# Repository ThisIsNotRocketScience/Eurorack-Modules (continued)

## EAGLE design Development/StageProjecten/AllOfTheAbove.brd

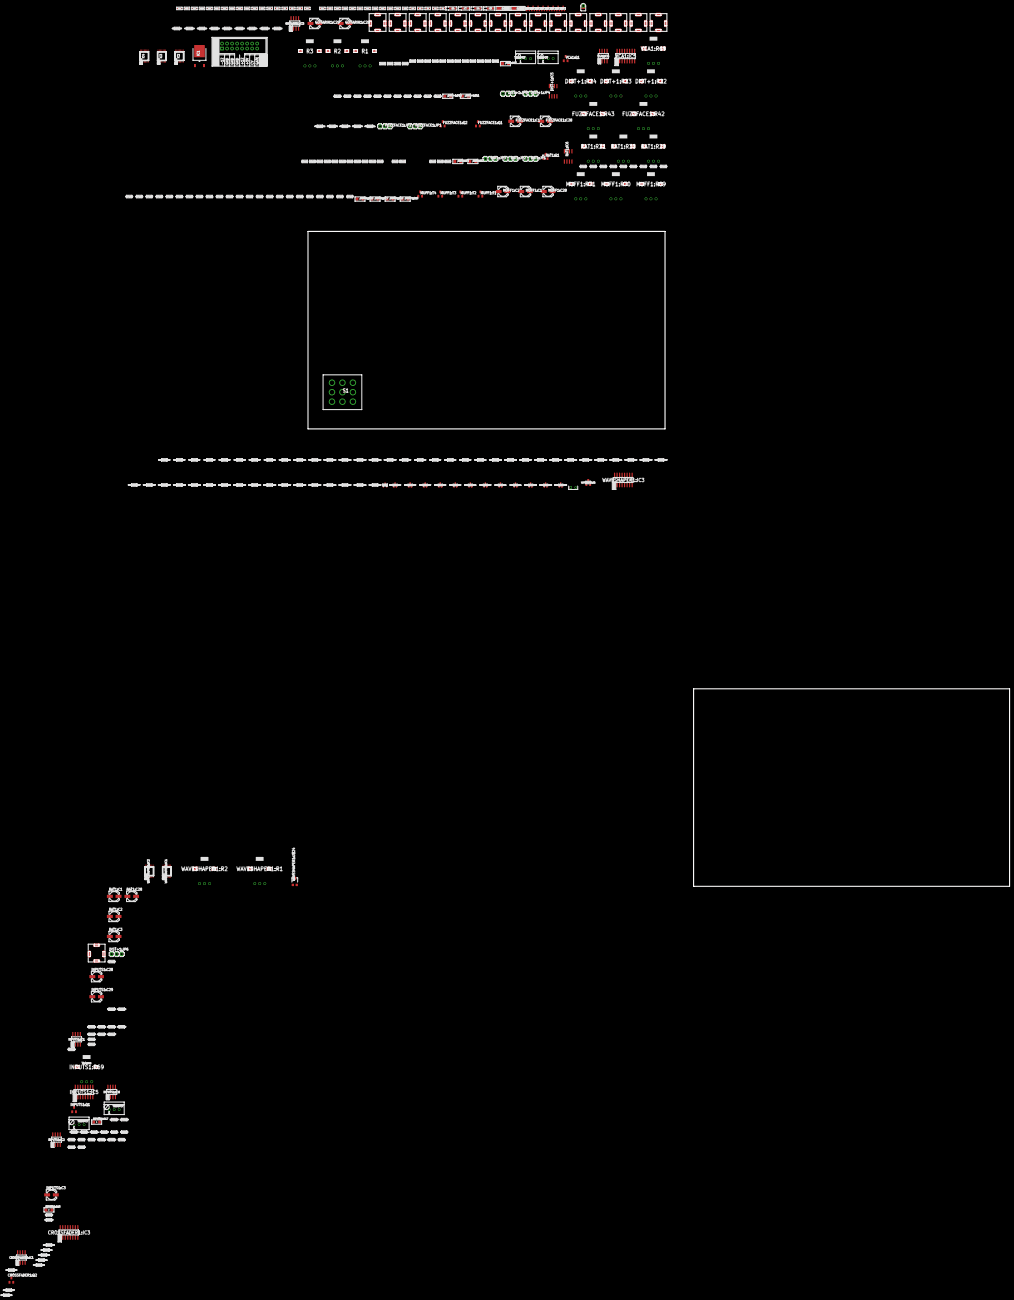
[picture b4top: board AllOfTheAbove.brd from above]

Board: 2 copper layers, 356 parts (0 on the bottom side), 213 nets, no tracks yet.

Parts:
C1, C2, C5, C6, C9, C10, C11, C12, C13, C14, C15, C16, C17, C18, C19, C20, C21: C0603
C3, C4, C7, C8: CASE-A_3216
CROSSFADER1:IC1: TL072; SO08
CROSSFADER1:IC3: LM13700M; SO16
CROSSFADER1:Q2: MMBT3906LT1SMD; SOT23-BEC
CROSSFADER1:R1, CROSSFADER1:R2, CROSSFADER1:R3, CROSSFADER1:R4, CROSSFADER1:R5, CROSSFADER1:R6, CROSSFADER1:R7, CROSSFADER1:R8: R0603
D1, D2: DO-214AC
D3, D4, D5, D6, D7, D8, D9, D10: BAS16W; SOT-323
DIST+1:C22, DIST+1:C28: 1nF; C0603
DIST+1:C23: 10nF; C0603
DIST+1:C24, DIST+1:C25: C0603
DIST+1:C26: 47nF; C0603
DIST+1:C27: 1uF; C0603
DIST+1:D11, DIST+1:D12: 1n34a; LL-34
DIST+1:IC5: UA741D; SO08
DIST+1:JP4, DIST+1:JP5, DIST+1:JP6: 1X03
DIST+1:R22: 10KB; ALPS_POT_SQUAREHOLES
DIST+1:R23: 1MC; ALPS_POT_SQUAREHOLES
DIST+1:R24: 10K; ALPS_POT_SQUAREHOLES
DIST+1:R25: 10K; R0603
DIST+1:R26: 4.7K; R0603
DIST+1:R27, DIST+1:R72: 1M; R0603
DIST+1:R28: 5.6K; R0603
FUZZFACE1:C1: 20uF; 153CLV-0505
FUZZFACE1:C28: 2.2uF; 153CLV-0505
FUZZFACE1:C42: 10nF; C0603
FUZZFACE1:JP1, FUZZFACE1:JP2: 1X03
FUZZFACE1:Q1, FUZZFACE1:Q2: MMBT3906LT1SMD; SOT23-BEC
FUZZFACE1:R41: 100K; R0603
FUZZFACE1:R42: 500KA; ALPS_POT_SQUAREHOLES
FUZZFACE1:R43: 1KB; ALPS_POT_SQUAREHOLES
FUZZFACE1:R44: 8.2K; R0603
FUZZFACE1:R45: 33K; R0603
FUZZFACE1:R46: 470R; R0603
GUITARIN1:C23: 10pF; C0603
GUITARIN1:C24: 47pF; C0603
GUITARIN1:C26, GUITARIN1:C27: 100n; C0603
GUITARIN1:C28, GUITARIN1:C29: 10uF; 153CLV-0505
GUITARIN1:IC5: TL071D; SO08
GUITARIN1:R22: 1M; R0603
GUITARIN1:R23: 150K; R0603
GUITARIN1:R24: 10K; R0603
GUITARIN1:R25: 470R; R0603
GUITARIN1:R26: 1K; R0603
IC1: 7809DT; TO252
IC2, IC3, IC4: TL074TSSOP14; TSSOP14
INPUTS1:C1, INPUTS1:C2, INPUTS1:C9, INPUTS1:C10: C0603
INPUTS1:C3, INPUTS1:C28, INPUTS1:C29: 10uF; 153CLV-0505
INPUTS1:C22, INPUTS1:C23: 10pF; C0603
INPUTS1:C24: 47pF; C0603
INPUTS1:C26, INPUTS1:C27: 100n; C0603
INPUTS1:D15: LL-34
INPUTS1:D17: 1N4148; LL-34
INPUTS1:IC1, INPUTS1:IC2, INPUTS1:IC6: TL072; SO08
INPUTS1:IC5: LM13700M; SO16
INPUTS1:Q1: MMBT3906LT1SMD; SOT23-BEC
INPUTS1:R1, INPUTS1:R2, INPUTS1:R7, INPUTS1:R8, INPUTS1:R27, INPUTS1:R31, INPUTS1:R32: 100K; R0603
INPUTS1:R3, INPUTS1:R10, INPUTS1:R26, INPUTS1:R28: 1K; R0603
INPUTS1:R4: 4.7K; R0603
INPUTS1:R5, INPUTS1:R6: 10R; R0603
INPUTS1:R9, INPUTS1:R33: 330K; R0603
INPUTS1:R22: 1M; R0603
INPUTS1:R23: 150K; R0603
INPUTS1:R24, INPUTS1:R30: 10K; R0603
INPUTS1:R25: 470R; R0603
INPUTS1:R29, INPUTS1:R34: TRIMPOT
INPUTS1:R69: ALPS_POT_SQUAREHOLES
J1, J3, J4, J5, J6, J7, J8, J9, J10, J11, J12, J13, J14, J15, J16, J17: JACK; 3.5MM-JACK-SWITCH-13MM-NOHOLES
J2: POWERSHROUDED; POWER_16_SHROUDED
MUFF1:C1, MUFF1:C2, MUFF1:C28: 1uF; 153CLV-0505
MUFF1:C44, MUFF1:C47, MUFF1:C50: 470pF; C0603
MUFF1:C45: 1uF; C0603
MUFF1:C46, MUFF1:C49, MUFF1:C53, MUFF1:C54: 100nF; C0603
MUFF1:C52: 4nF; C0603
MUFF1:C55: 10nF; C0603
MUFF1:D15, MUFF1:D16, MUFF1:D17, MUFF1:D18: LL-34
MUFF1:R47, MUFF1:R63: 39K; R0603
MUFF1:R48: 47K; R0603
MUFF1:R49, MUFF1:R56, MUFF1:R61: 470K; R0603
MUFF1:R50: 100R; R0603
MUFF1:R51, MUFF1:R53, MUFF1:R57, MUFF1:R58, MUFF1:R62: 10K; R0603
MUFF1:R52: 1K; R0603
MUFF1:R54, MUFF1:R59, MUFF1:R65: 100K; R0603
MUFF1:R55, MUFF1:R60: 150R; R0603
MUFF1:R64: 22K; R0603
MUFF1:R66: 430K; R0603
MUFF1:R67: 15K; R0603
MUFF1:R68: 3.3K; R0603
MUFF1:R69, MUFF1:R70, MUFF1:R71: 100KB; ALPS_POT_SQUAREHOLES
MUFF1:T1, MUFF1:T2, MUFF1:T3, MUFF1:T4: 2n3904; SOT23-BEC
PCB1: EURORACK_PCB36HP_10CM; EURORACK36HP
R1, R2, R3: ALPS_POT_SQUAREHOLES
R4, R5, R6, R7, R8, R9, R10, R11, R12, R13, R14, R15, R16, R17, R18, R19, R20, R21: R0603
RAT1:C1, RAT1:C3: 4.7uF; 153CLV-0505
RAT1:C2: 2.2uF; 153CLV-0505
RAT1:C28: 1uF; 153CLV-0505
RAT1:C29, RAT1:C36: 22nF; C0603
RAT1:C30: 1nF; C0603
RAT1:C31: 100pF; C0603
RAT1:C35: 3.3nF; C0603
RAT1:C38, RAT1:C39: C0603
RAT1:D13, RAT1:D14: 1n4148; LL-34
RAT1:IC6: UA741D; SO08
RAT1:JP1, RAT1:JP2, RAT1:JP3: 1X03
RAT1:Q1: SST201; SOT23
RAT1:R29, RAT1:R30, RAT1:R31: 100KA; ALPS_POT_SQUAREHOLES
RAT1:R32, RAT1:R34, RAT1:R39: 1M; R0603
RAT1:R33, RAT1:R37: 1K; R0603
RAT1:R35: 560R; R0603
RAT1:R36: 47R; R0603
RAT1:R38: 1.5K; R0603
RAT1:R40: 10K; R0603
S1: 3PDT
U$13: VOLTAGETESTPAD; POWERTESTPAD
VCA1:C1, VCA1:C2, VCA1:C9, VCA1:C10: C0603
VCA1:C22: 10pF; C0603
VCA1:D17: 1N4148; LL-34
VCA1:IC5: LM13700M; SO16
VCA1:IC6: TL072; SO08
VCA1:Q1: MMBT3906LT1SMD; SOT23-BEC
VCA1:R22: 4.7K; R0603
VCA1:R23, VCA1:R24: 10R; R0603
VCA1:R25, VCA1:R26, VCA1:R27, VCA1:R31, VCA1:R32: 100K; R0603
VCA1:R28: 1K; R0603
VCA1:R29, VCA1:R34: TRIMPOT
VCA1:R30: 10K; R0603
VCA1:R33: 330K; R0603
VCA1:R69: ALPS_POT_SQUAREHOLES
WAVESHAPER1:12V: POWER12V; FENIXINTERNALCONNECTIONPAD
WAVESHAPER1:-12V: POWER-12V; FENIXINTERNALCONNECTIONPAD
WAVESHAPER1:C1, WAVESHAPER1:C2, WAVESHAPER1:C3, WAVESHAPER1:C4, WAVESHAPER1:C5, WAVESHAPER1:C6, WAVESHAPER1:C13: 100n; C0603
WAVESHAPER1:C7, WAVESHAPER1:C9, WAVESHAPER1:C10, WAVESHAPER1:C11, WAVESHAPER1:C12: 33p; C0603
WAVESHAPER1:C8: 220p; C0603
WAVESHAPER1:C14: 680n; C0603
WAVESHAPER1:C15, WAVESHAPER1:C16: 33p FIX; C0603
WAVESHAPER1:D1, WAVESHAPER1:D2, WAVESHAPER1:D3, WAVESHAPER1:D4, WAVESHAPER1:D5, WAVESHAPER1:D6, WAVESHAPER1:D7, WAVESHAPER1:D8, WAVESHAPER1:D9, WAVESHAPER1:D10, WAVESHAPER1:D11, WAVESHAPER1:D12: BAS16W; SOT-323
WAVESHAPER1:GND: POWERGND; FENIXINTERNALCONNECTIONPAD
WAVESHAPER1:IC1, WAVESHAPER1:IC2: TL074TSSOP14; TSSOP14
WAVESHAPER1:IC3: LM13700M; SO16
WAVESHAPER1:R1: 100KB Lin; ALPS_POT_SQUAREHOLES
WAVESHAPER1:R2: 10KB Lin; ALPS_POT_SQUAREHOLES
WAVESHAPER1:R4: 14; R0603
WAVESHAPER1:R5, WAVESHAPER1:R9: 470K; R0603
WAVESHAPER1:R6: 4K7; R0603
WAVESHAPER1:R7, WAVESHAPER1:R8, WAVESHAPER1:R22: 100; R0603
WAVESHAPER1:R10: 22K; R0603
WAVESHAPER1:R11, WAVESHAPER1:R15, WAVESHAPER1:R16, WAVESHAPER1:R29, WAVESHAPER1:R31, WAVESHAPER1:R33, WAVESHAPER1:R34: 33K; R0603
WAVESHAPER1:R12: 4M7; R0603
WAVESHAPER1:R13, WAVESHAPER1:R24, WAVESHAPER1:R26: 10K; R0603
WAVESHAPER1:R14: 47K; R0603
WAVESHAPER1:R17, WAVESHAPER1:R18, WAVESHAPER1:R19, WAVESHAPER1:R20, WAVESHAPER1:R21, WAVESHAPER1:R23, WAVESHAPER1:R28, WAVESHAPER1:R30, WAVESHAPER1:R32, WAVESHAPER1:R35, WAVESHAPER1:R36: 100K; R0603
WAVESHAPER1:R25: 220K; R0603
WAVESHAPER1:R27: 6K8; R0603
WAVESHAPER1:R37: 27k; R0603
WAVESHAPER1:R38: 150k; R0603
WAVESHAPER1:T1: 3906; SOT23-BEC
WAVESHAPER1:U$1: MODULEEND
WAVESHAPER1:U$2: FENIXGRID
WAVESHAPER1:U$3: TESTPOINT_DUAL_PTH; TESTPAD_DUAL_PTH
WAVESHAPER1:U$11: BAT54S; SOT23
WAVESHAPER1:U$24: 50K; TC33X
WAVESHAPER1:WSAIN: SIGNALIN; FENIXINTERNALCONNECTIONPAD
WAVESHAPER1:WSCV, WAVESHAPER1:WSIN: CVIN; FENIXINTERNALCONNECTIONPAD
WAVESHAPER1:WSOUT: SIGNALOUT; FENIXINTERNALCONNECTIONPAD

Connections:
9V: C5.2, C7.+, IC1.2
12V: C1.2, C3.+, C6.2, C8.+, C9.2, C11.2, D1.2, IC1.1, IC2.4, IC3.4
-12V: C2.1, C4.-, C10.1, C12.1, D2.1, IC2.11, IC3.11
CROSSFADER1:GND: CROSSFADER1:IC1.3, CROSSFADER1:IC1.5, CROSSFADER1:R1.1, CROSSFADER1:R2.1
CROSSFADER1:N$1: CROSSFADER1:IC3.4, CROSSFADER1:R1.2, CROSSFADER1:R3.1
CROSSFADER1:N$2: CROSSFADER1:IC3.3, CROSSFADER1:R2.2, CROSSFADER1:R4.1
CROSSFADER1:N$3: CROSSFADER1:R3.2, CROSSFADER1:R5.1
CROSSFADER1:N$4: CROSSFADER1:IC1.2, CROSSFADER1:IC3.5, CROSSFADER1:R5.2, CROSSFADER1:R6.2
CROSSFADER1:N$5: CROSSFADER1:IC1.1, CROSSFADER1:R6.1
CROSSFADER1:N$6: CROSSFADER1:IC3.1, CROSSFADER1:Q2.C
CROSSFADER1:N$7: CROSSFADER1:IC1.7, CROSSFADER1:Q2.B
CROSSFADER1:N$8: CROSSFADER1:IC1.6, CROSSFADER1:R7.2, CROSSFADER1:R8.1
CROSSFADER1:N$10: CROSSFADER1:Q2.E, CROSSFADER1:R7.1
DIST+1:12V: DIST+1:C24.2, DIST+1:JP4.3
DIST+1:-12V: DIST+1:C25.1, DIST+1:JP5.3
DIST+1:GND: DIST+1:C22.2, DIST+1:C24.1, DIST+1:C25.2, DIST+1:C28.1, DIST+1:D11.A, DIST+1:D12.C, DIST+1:JP5.1, DIST+1:R23.P$1, DIST+1:R23.P$2, DIST+1:R24.P$1
DIST+1:INPUT_A: DIST+1:C22.1, DIST+1:C23.1
DIST+1:N$20: DIST+1:C23.2, DIST+1:R25.2
DIST+1:N$21: DIST+1:IC5.3, DIST+1:JP6.2, DIST+1:R25.1
DIST+1:N$22: DIST+1:C26.2, DIST+1:IC5.2, DIST+1:R27.1
DIST+1:N$23: DIST+1:C26.1, DIST+1:R26.1
DIST+1:N$32: DIST+1:C27.1, DIST+1:IC5.6, DIST+1:R27.2
DIST+1:N$33: DIST+1:R23.P$3, DIST+1:R26.2
DIST+1:N$34: DIST+1:C28.2, DIST+1:D11.C, DIST+1:D12.A, DIST+1:R22.P$3, DIST+1:R24.P$3
DIST+1:N$35: DIST+1:C27.2, DIST+1:R28.2
DIST+1:N$36: DIST+1:R22.P$1, DIST+1:R22.P$2, DIST+1:R28.1
DIST+1:N$81: DIST+1:IC5.7, DIST+1:JP4.2
DIST+1:N$82: DIST+1:IC5.4, DIST+1:JP5.2
DIST+1:N$87: DIST+1:JP6.1, DIST+1:R72.1
FUZZFACE1:9V: FUZZFACE1:C1.+, FUZZFACE1:JP2.3, FUZZFACE1:Q1.E, FUZZFACE1:R42.P$1, FUZZFACE1:R43.P$1
FUZZFACE1:GND: FUZZFACE1:R45.1, FUZZFACE1:R46.1
FUZZFACE1:N$53: FUZZFACE1:JP1.3, FUZZFACE1:Q2.E, FUZZFACE1:R41.1, FUZZFACE1:R43.P$3
FUZZFACE1:N$54: FUZZFACE1:C28.-, FUZZFACE1:JP2.2, FUZZFACE1:Q1.B, FUZZFACE1:R41.2
FUZZFACE1:N$55: FUZZFACE1:JP1.2, FUZZFACE1:JP2.1, FUZZFACE1:Q1.C, FUZZFACE1:Q2.B, FUZZFACE1:R45.2
FUZZFACE1:N$56: FUZZFACE1:C1.-, FUZZFACE1:R43.P$2
FUZZFACE1:N$57: FUZZFACE1:C42.2, FUZZFACE1:R42.P$3
FUZZFACE1:N$58: FUZZFACE1:C42.1, FUZZFACE1:R44.1, FUZZFACE1:R46.2
FUZZFACE1:N$59: FUZZFACE1:JP1.1, FUZZFACE1:Q2.C, FUZZFACE1:R44.2
GND: C1.1, C2.2, C3.-, C4.+, C5.1, C6.1, C7.-, C8.-, C9.1, C10.2, C11.1, C12.2, C14.1, C15.1, C16.1, C17.1, D3.ANODE, D5.ANODE, D7.ANODE, D9.ANODE, IC1.3, IC3.2, IC3.6, IC3.10, IC3.12, IC4.3, J1.RING_B@1, J1.RING_T@3, J1.SWITCH_B@1, J1.SWITCH_T@3, J2.3, J2.4, J2.5, J2.6, J2.7, J2.8, J3.RING_B@1, J3.RING_T@3, J4.RING_B@1, J4.RING_T@3, J5.RING_B@1, J5.RING_T@3, J6.RING_B@1, J6.RING_T@3, J7.RING_B@1, J7.RING_T@3, J8.RING_B@1, J8.RING_T@3, J9.RING_B@1, J9.RING_T@3, J10.RING_B@1, J10.RING_T@3, J11.RING_B@1, J11.RING_T@3, J12.RING_B@1, J12.RING_T@3, J13.RING_B@1, J13.RING_T@3, J14.RING_B@1, J14.RING_T@3, J15.RING_B@1, J15.RING_T@3, J16.RING_B@1, J16.RING_T@3, R12.1, R13.1, R14.1, R15.1
GUITARIN1:12V: GUITARIN1:C26.2, GUITARIN1:IC5.7
GUITARIN1:-12V: GUITARIN1:C27.1, GUITARIN1:IC5.4
GUITARIN1:GND: GUITARIN1:C23.1, GUITARIN1:C26.1, GUITARIN1:C27.2, GUITARIN1:C29.-, GUITARIN1:R22.1, GUITARIN1:R23.1
GUITARIN1:GUITAR_IN: GUITARIN1:C28.-, GUITARIN1:R22.2
GUITARIN1:N$20: GUITARIN1:C23.2, GUITARIN1:C28.+, GUITARIN1:IC5.3, GUITARIN1:R23.2
GUITARIN1:N$21: GUITARIN1:C29.+, GUITARIN1:R25.1
GUITARIN1:N$22: GUITARIN1:C24.1, GUITARIN1:IC5.6, GUITARIN1:R24.2, GUITARIN1:R26.1
GUITARIN1:N$23: GUITARIN1:C24.2, GUITARIN1:IC5.2, GUITARIN1:R24.1, GUITARIN1:R25.2
INPUTS1:12V: INPUTS1:C1.2, INPUTS1:C9.2, INPUTS1:C26.2, INPUTS1:IC1.8, INPUTS1:IC2.8, INPUTS1:IC5.11, INPUTS1:IC6.8, INPUTS1:R29.P$3, INPUTS1:R34.P$3
INPUTS1:-12V: INPUTS1:C2.1, INPUTS1:C10.1, INPUTS1:C27.1, INPUTS1:IC1.4, INPUTS1:IC2.4, INPUTS1:IC5.6, INPUTS1:IC6.4, INPUTS1:R29.P$1, INPUTS1:R34.P$1
INPUTS1:GND: INPUTS1:C1.1, INPUTS1:C2.2, INPUTS1:C3.-, INPUTS1:C9.1, INPUTS1:C10.2, INPUTS1:C23.1, INPUTS1:C26.1, INPUTS1:C27.2, INPUTS1:C29.-, INPUTS1:IC6.5, INPUTS1:R5.1, INPUTS1:R6.2, INPUTS1:R8.2, INPUTS1:R9.1, INPUTS1:R22.1, INPUTS1:R23.1, INPUTS1:R30.1, INPUTS1:R69.P$1
INPUTS1:GUITAR_IN: INPUTS1:C28.-, INPUTS1:R22.2
INPUTS1:GUITAR_OUT: INPUTS1:R1.2, INPUTS1:R26.2
INPUTS1:MIX_OUT: INPUTS1:D15.A, INPUTS1:IC2.1, INPUTS1:IC2.2, INPUTS1:R4.1
INPUTS1:N$1: INPUTS1:IC1.6, INPUTS1:IC1.7, INPUTS1:R2.2
INPUTS1:N$2: INPUTS1:IC1.5, INPUTS1:R3.2
INPUTS1:N$3: INPUTS1:IC2.6, INPUTS1:IC2.7, INPUTS1:R10.2
INPUTS1:N$4: INPUTS1:IC5.4, INPUTS1:R6.1, INPUTS1:R7.1
INPUTS1:N$5: INPUTS1:IC5.3, INPUTS1:R4.2, INPUTS1:R5.2
INPUTS1:N$6: INPUTS1:IC5.5, INPUTS1:IC6.3, INPUTS1:R8.1
INPUTS1:N$7: INPUTS1:C22.1, INPUTS1:IC6.2, INPUTS1:R27.1
INPUTS1:N$8: INPUTS1:C3.+, INPUTS1:D15.C, INPUTS1:IC2.5, INPUTS1:R9.2
INPUTS1:N$20: INPUTS1:C23.2, INPUTS1:C28.+, INPUTS1:IC1.3, INPUTS1:R23.2
INPUTS1:N$21: INPUTS1:C29.+, INPUTS1:R25.1
INPUTS1:N$22: INPUTS1:C24.1, INPUTS1:IC1.1, INPUTS1:R24.2, INPUTS1:R26.1
INPUTS1:N$23: INPUTS1:C24.2, INPUTS1:IC1.2, INPUTS1:R24.1, INPUTS1:R25.2
INPUTS1:N$32: INPUTS1:R7.2, INPUTS1:R29.P$2
INPUTS1:N$33: INPUTS1:C22.2, INPUTS1:IC6.1, INPUTS1:R27.2, INPUTS1:R28.1
INPUTS1:N$36: INPUTS1:D17.A, INPUTS1:IC6.7, INPUTS1:Q1.B
INPUTS1:N$37: INPUTS1:D17.C, INPUTS1:IC6.6, INPUTS1:R31.1, INPUTS1:R32.2, INPUTS1:R33.2
INPUTS1:N$38: INPUTS1:Q1.E, INPUTS1:R30.2, INPUTS1:R31.2
INPUTS1:N$39: INPUTS1:IC5.1, INPUTS1:Q1.C
INPUTS1:N$40: INPUTS1:R33.1, INPUTS1:R34.P$2
INPUTS1:N$42: INPUTS1:R32.1, INPUTS1:R69.P$2
INPUTS1:VCA_SIG_IN: INPUTS1:IC2.3, INPUTS1:R1.1, INPUTS1:R2.1
INPUT_A: J6.TIP_B@1, J6.TIP_T@3
INPUT_B: J4.TIP_B@1, J4.TIP_T@3
INPUT_C: J11.TIP_B@1, J11.TIP_T@3
INPUT_D: J14.TIP_B@1, J14.TIP_T@3
MASTERINPUT: J1.TIP_B@1, J1.TIP_T@3, J6.SWITCH_B@1, J6.SWITCH_T@3
MUFF1:9V: MUFF1:R51.1, MUFF1:R57.1, MUFF1:R62.1, MUFF1:R66.2, MUFF1:R67.2
MUFF1:GND: MUFF1:C55.1, MUFF1:R48.1, MUFF1:R50.2, MUFF1:R52.2, MUFF1:R54.1, MUFF1:R55.1, MUFF1:R59.1, MUFF1:R60.1, MUFF1:R64.2, MUFF1:R65.1, MUFF1:R68.1, MUFF1:R69.P$1
MUFF1:N$1: MUFF1:C28.-, MUFF1:R47.2
MUFF1:N$61: MUFF1:C28.+, MUFF1:C44.1, MUFF1:R48.2, MUFF1:R49.2, MUFF1:T1.B
MUFF1:N$62: MUFF1:R50.1, MUFF1:T1.E
MUFF1:N$63: MUFF1:C44.2, MUFF1:C45.1, MUFF1:R49.1, MUFF1:R51.2, MUFF1:T1.C
MUFF1:N$64: MUFF1:C45.2, MUFF1:R71.P$3
MUFF1:N$65: MUFF1:C1.-, MUFF1:C47.1, MUFF1:R53.2, MUFF1:R54.2, MUFF1:R56.2, MUFF1:T2.B
MUFF1:N$66: MUFF1:C1.+, MUFF1:D15.A, MUFF1:D16.C
MUFF1:N$67: MUFF1:R55.2, MUFF1:T2.E
MUFF1:N$68: MUFF1:C47.2, MUFF1:C49.1, MUFF1:D15.C, MUFF1:D16.A, MUFF1:R56.1, MUFF1:R57.2, MUFF1:T2.C
MUFF1:N$69: MUFF1:C49.2, MUFF1:R58.1
MUFF1:N$70: MUFF1:C2.-, MUFF1:C50.1, MUFF1:R58.2, MUFF1:R59.2, MUFF1:R61.2, MUFF1:T3.B
MUFF1:N$71: MUFF1:R60.2, MUFF1:T3.E
MUFF1:N$72: MUFF1:C50.2, MUFF1:C52.1, MUFF1:D17.C, MUFF1:D18.A, MUFF1:R61.1, MUFF1:R62.2, MUFF1:R63.1, MUFF1:T3.C
MUFF1:N$73: MUFF1:C53.1, MUFF1:R70.P$2
MUFF1:N$74: MUFF1:C55.2, MUFF1:R63.2, MUFF1:R70.P$1
MUFF1:N$75: MUFF1:C52.2, MUFF1:R64.1, MUFF1:R70.P$3
MUFF1:N$76: MUFF1:C2.+, MUFF1:D17.A, MUFF1:D18.C
MUFF1:N$77: MUFF1:C53.2, MUFF1:R65.2, MUFF1:R66.1, MUFF1:T4.B
MUFF1:N$78: MUFF1:C54.1, MUFF1:R67.1, MUFF1:T4.C
MUFF1:N$79: MUFF1:R68.2, MUFF1:T4.E
MUFF1:N$80: MUFF1:C54.2, MUFF1:R69.P$3
MUFF1:N$84: MUFF1:R52.1, MUFF1:R71.P$1
MUFF1:N$85: MUFF1:C46.2, MUFF1:R53.1
MUFF1:N$86: MUFF1:C46.1, MUFF1:R71.P$2
unnamed: IC3.3, R4.2
unnamed: D1.1, J2.9, J2.10
unnamed: D2.2, J2.1, J2.2
unnamed: IC3.5, R5.2
unnamed: IC3.1, R6.1
unnamed: IC3.7, R7.1
unnamed: IC3.9, R9.2
unnamed: IC3.13, R8.2
unnamed: IC3.14, R11.1
unnamed: IC3.8, R10.1
unnamed: IC4.1, R5.1, R8.1, R16.1
unnamed: C13.2, IC4.2, R16.2
unnamed: IC4.8, R17.1
unnamed: IC4.9, R17.2
unnamed: C14.2, D3.CATHODE, D4.ANODE, R6.2
unnamed: C13.1, R4.1, R9.1
unnamed: C15.2, D5.CATHODE, D6.ANODE, R7.2
unnamed: C16.2, D7.CATHODE, D8.ANODE, R10.2
unnamed: C17.2, D9.CATHODE, D10.ANODE, R11.2
unnamed: C19.2, D6.CATHODE, R14.2
unnamed: C20.2, D8.CATHODE, R13.2
unnamed: C21.2, D10.CATHODE, R12.2
unnamed: C18.2, D4.CATHODE, R15.2
unnamed: C18.1, R18.2
unnamed: C19.1, R19.2
unnamed: C20.1, R20.2
unnamed: C21.1, R21.2
OUTPUT_A: J4.SWITCH_B@1, J4.SWITCH_T@3, J7.TIP_B@1, J7.TIP_T@3
OUTPUT_B: J9.TIP_B@1, J9.TIP_T@3, J11.SWITCH_B@1, J11.SWITCH_T@3
OUTPUT_C: J13.TIP_B@1, J13.TIP_T@3, J14.SWITCH_B@1, J14.SWITCH_T@3
OUTPUT_D: J3.TIP_B@1, J3.TIP_T@3, J16.TIP_B@1, J16.TIP_T@3
RAT1:9V: RAT1:JP2.1, RAT1:Q1.1
RAT1:12V: RAT1:C38.2, RAT1:JP2.3
RAT1:-12V: RAT1:C39.1, RAT1:JP3.3
RAT1:GND: RAT1:C2.-, RAT1:C3.-, RAT1:C30.1, RAT1:C35.2, RAT1:C38.1, RAT1:C39.2, RAT1:D13.A, RAT1:D14.C, RAT1:JP3.1, RAT1:R29.P$1, RAT1:R32.2, RAT1:R39.1, RAT1:R40.1
RAT1:INPUT_B: RAT1:C29.1, RAT1:R32.1
RAT1:N$37: RAT1:C29.2, RAT1:JP1.2, RAT1:R33.1
RAT1:N$38: RAT1:C30.2, RAT1:IC6.3, RAT1:R33.2
RAT1:N$39: RAT1:IC6.7, RAT1:JP2.2
RAT1:N$40: RAT1:IC6.4, RAT1:JP3.2
RAT1:N$41: RAT1:JP1.1, RAT1:R34.1
RAT1:N$42: RAT1:C31.1, RAT1:IC6.2, RAT1:R31.P$1, RAT1:R31.P$2, RAT1:R35.2, RAT1:R36.2
RAT1:N$43: RAT1:C1.+, RAT1:C31.2, RAT1:IC6.6, RAT1:R31.P$3
RAT1:N$44: RAT1:C1.-, RAT1:R37.1
RAT1:N$45: RAT1:D13.C, RAT1:D14.A, RAT1:R30.P$1, RAT1:R30.P$2, RAT1:R37.2
RAT1:N$46: RAT1:R30.P$3, RAT1:R38.1
RAT1:N$47: RAT1:C2.+, RAT1:R36.1
RAT1:N$48: RAT1:C3.+, RAT1:R35.1
RAT1:N$49: RAT1:C35.1, RAT1:C36.1, RAT1:R38.2
RAT1:N$50: RAT1:C36.2, RAT1:Q1.3, RAT1:R39.2
RAT1:N$51: RAT1:C28.+, RAT1:Q1.2, RAT1:R40.2
RAT1:N$52: RAT1:C28.-, RAT1:R29.P$3
VCA1:12V: VCA1:C1.2, VCA1:C9.2, VCA1:IC5.11, VCA1:IC6.8, VCA1:R29.P$3, VCA1:R34.P$3
VCA1:-12V: VCA1:C2.1, VCA1:C10.1, VCA1:IC5.6, VCA1:IC6.4, VCA1:R29.P$1, VCA1:R34.P$1
VCA1:GND: VCA1:C1.1, VCA1:C2.2, VCA1:C9.1, VCA1:C10.2, VCA1:IC6.5, VCA1:R23.1, VCA1:R24.2, VCA1:R26.2, VCA1:R30.1, VCA1:R69.P$1
VCA1:N$20: VCA1:IC5.4, VCA1:R24.1, VCA1:R25.1
VCA1:N$21: VCA1:IC5.3, VCA1:R22.2, VCA1:R23.2
VCA1:N$22: VCA1:IC5.5, VCA1:IC6.3, VCA1:R26.1
VCA1:N$23: VCA1:C22.1, VCA1:IC6.2, VCA1:R27.1
VCA1:N$32: VCA1:R25.2, VCA1:R29.P$2
VCA1:N$33: VCA1:C22.2, VCA1:IC6.1, VCA1:R27.2, VCA1:R28.1
VCA1:N$36: VCA1:D17.A, VCA1:IC6.7, VCA1:Q1.B
VCA1:N$37: VCA1:D17.C, VCA1:IC6.6, VCA1:R31.1, VCA1:R32.2, VCA1:R33.2
VCA1:N$38: VCA1:Q1.E, VCA1:R30.2, VCA1:R31.2
VCA1:N$39: VCA1:IC5.1, VCA1:Q1.C
VCA1:N$40: VCA1:R33.1, VCA1:R34.P$2
VCA1:N$42: VCA1:R32.1, VCA1:R69.P$2
WAVESHAPER1:12V: WAVESHAPER1:12V.P$1, WAVESHAPER1:C1.2, WAVESHAPER1:C3.2, WAVESHAPER1:C5.2, WAVESHAPER1:IC1.4, WAVESHAPER1:IC2.4, WAVESHAPER1:IC3.11, WAVESHAPER1:R2.P$3, WAVESHAPER1:U$24.1
WAVESHAPER1:-12V: WAVESHAPER1:-12V.P$1, WAVESHAPER1:C2.1, WAVESHAPER1:C4.1, WAVESHAPER1:C6.1, WAVESHAPER1:IC1.11, WAVESHAPER1:IC2.11, WAVESHAPER1:IC3.6, WAVESHAPER1:R9.2, WAVESHAPER1:R12.1, WAVESHAPER1:U$24.3
WAVESHAPER1:BIASMAINLINE: WAVESHAPER1:C7.1, WAVESHAPER1:D2.ANODE, WAVESHAPER1:D4.ANODE, WAVESHAPER1:D6.ANODE, WAVESHAPER1:D7.ANODE, WAVESHAPER1:D8.ANODE, WAVESHAPER1:IC1.8, WAVESHAPER1:R13.1
WAVESHAPER1:GND: WAVESHAPER1:C1.1, WAVESHAPER1:C2.2, WAVESHAPER1:C3.1, WAVESHAPER1:C4.2, WAVESHAPER1:C5.1, WAVESHAPER1:C6.2, WAVESHAPER1:D1.CATHODE, WAVESHAPER1:D3.CATHODE, WAVESHAPER1:D5.CATHODE, WAVESHAPER1:D9.CATHODE, WAVESHAPER1:D10.CATHODE, WAVESHAPER1:D11.ANODE, WAVESHAPER1:D12.ANODE, WAVESHAPER1:GND.P$1, WAVESHAPER1:IC1.5, WAVESHAPER1:IC1.10, WAVESHAPER1:IC3.7, WAVESHAPER1:IC3.10, WAVESHAPER1:IC3.13, WAVESHAPER1:IC3.14, WAVESHAPER1:R1.P$1, WAVESHAPER1:R2.P$1, WAVESHAPER1:R4.2, WAVESHAPER1:R5.2, WAVESHAPER1:R7.1, WAVESHAPER1:R8.1, WAVESHAPER1:R24.2, WAVESHAPER1:R25.1, WAVESHAPER1:R26.1, WAVESHAPER1:U$3.P$2
WAVESHAPER1:INPUT_E: WAVESHAPER1:R14.2, WAVESHAPER1:WSAIN.P$1
WAVESHAPER1:N$1: WAVESHAPER1:R4.1, WAVESHAPER1:U$11.P$3
WAVESHAPER1:N$3: WAVESHAPER1:C7.2, WAVESHAPER1:IC1.9, WAVESHAPER1:R13.2, WAVESHAPER1:R14.1
WAVESHAPER1:N$5: WAVESHAPER1:R1.P$2, WAVESHAPER1:R10.2
WAVESHAPER1:N$6: WAVESHAPER1:R1.P$3, WAVESHAPER1:WSCV.P$1
WAVESHAPER1:N$7: WAVESHAPER1:D12.CATHODE, WAVESHAPER1:R10.1, WAVESHAPER1:R11.1, WAVESHAPER1:R12.2, WAVESHAPER1:T1.E
WAVESHAPER1:N$8: WAVESHAPER1:R2.P$2, WAVESHAPER1:R11.2
WAVESHAPER1:N$9: WAVESHAPER1:C13.2, WAVESHAPER1:R26.2, WAVESHAPER1:R27.2, WAVESHAPER1:U$11.P$1, WAVESHAPER1:U$11.P$2
WAVESHAPER1:N$10: WAVESHAPER1:R6.1, WAVESHAPER1:T1.C
WAVESHAPER1:N$11: WAVESHAPER1:C8.1, WAVESHAPER1:IC1.7, WAVESHAPER1:R15.1, WAVESHAPER1:R16.2, WAVESHAPER1:R17.2
WAVESHAPER1:N$12: WAVESHAPER1:C8.2, WAVESHAPER1:C14.2, WAVESHAPER1:IC1.6, WAVESHAPER1:R15.2
WAVESHAPER1:N$13: WAVESHAPER1:C14.1, WAVESHAPER1:IC3.5, WAVESHAPER1:R5.1
WAVESHAPER1:N$14: WAVESHAPER1:D3.ANODE, WAVESHAPER1:D4.CATHODE, WAVESHAPER1:IC2.3, WAVESHAPER1:R16.1
WAVESHAPER1:N$15: WAVESHAPER1:C9.1, WAVESHAPER1:IC2.1, WAVESHAPER1:R18.1, WAVESHAPER1:R31.2, WAVESHAPER1:R32.2
WAVESHAPER1:N$16: WAVESHAPER1:D5.ANODE, WAVESHAPER1:D6.CATHODE, WAVESHAPER1:IC2.5, WAVESHAPER1:R31.1
WAVESHAPER1:N$17: WAVESHAPER1:C9.2, WAVESHAPER1:IC2.2, WAVESHAPER1:R17.1, WAVESHAPER1:R18.2
WAVESHAPER1:N$18: WAVESHAPER1:C11.2, WAVESHAPER1:IC2.9, WAVESHAPER1:R20.1, WAVESHAPER1:R36.2
WAVESHAPER1:N$19: WAVESHAPER1:C16.1, WAVESHAPER1:IC1.1, WAVESHAPER1:R27.1, WAVESHAPER1:R28.2, WAVESHAPER1:U$3.P$1
WAVESHAPER1:N$20: WAVESHAPER1:D8.CATHODE, WAVESHAPER1:D9.ANODE, WAVESHAPER1:IC2.12, WAVESHAPER1:R34.1
WAVESHAPER1:N$21: WAVESHAPER1:C10.2, WAVESHAPER1:IC2.6, WAVESHAPER1:R19.2, WAVESHAPER1:R32.1
WAVESHAPER1:N$22: WAVESHAPER1:C10.1, WAVESHAPER1:IC2.7, WAVESHAPER1:R19.1, WAVESHAPER1:R20.2, WAVESHAPER1:R33.2
WAVESHAPER1:N$23: WAVESHAPER1:D7.CATHODE, WAVESHAPER1:D10.ANODE, WAVESHAPER1:IC2.10, WAVESHAPER1:R33.1
WAVESHAPER1:N$24: WAVESHAPER1:C11.1, WAVESHAPER1:IC2.8, WAVESHAPER1:R34.2, WAVESHAPER1:R35.2, WAVESHAPER1:R36.1
WAVESHAPER1:N$25: WAVESHAPER1:C13.1, WAVESHAPER1:IC1.12, WAVESHAPER1:R25.2
WAVESHAPER1:N$26: WAVESHAPER1:C15.2, WAVESHAPER1:IC2.13, WAVESHAPER1:R21.2, WAVESHAPER1:R35.1
WAVESHAPER1:N$27: WAVESHAPER1:C15.1, WAVESHAPER1:IC2.14, WAVESHAPER1:R21.1, WAVESHAPER1:R29.1, WAVESHAPER1:R30.1
WAVESHAPER1:N$28: WAVESHAPER1:D1.ANODE, WAVESHAPER1:D2.CATHODE, WAVESHAPER1:IC1.3, WAVESHAPER1:R29.2
WAVESHAPER1:N$29: WAVESHAPER1:C12.1, WAVESHAPER1:IC1.14, WAVESHAPER1:R22.2
WAVESHAPER1:N$30: WAVESHAPER1:C16.2, WAVESHAPER1:IC1.2, WAVESHAPER1:R28.1, WAVESHAPER1:R30.2
WAVESHAPER1:N$32: WAVESHAPER1:C12.2, WAVESHAPER1:IC1.13, WAVESHAPER1:R23.2, WAVESHAPER1:R24.1
WAVESHAPER1:N$33: WAVESHAPER1:D11.CATHODE, WAVESHAPER1:R9.1, WAVESHAPER1:T1.B
WAVESHAPER1:N$34: WAVESHAPER1:IC3.1, WAVESHAPER1:R6.2
WAVESHAPER1:N$35: WAVESHAPER1:R37.2, WAVESHAPER1:WSIN.P$1
WAVESHAPER1:N$36: WAVESHAPER1:IC3.3, WAVESHAPER1:R7.2, WAVESHAPER1:R37.1
WAVESHAPER1:N$37: WAVESHAPER1:R38.2, WAVESHAPER1:U$24.2
WAVESHAPER1:N$38: WAVESHAPER1:IC3.4, WAVESHAPER1:R8.2, WAVESHAPER1:R38.1
WAVESHAPER1:OUTPUT_E: WAVESHAPER1:R22.1, WAVESHAPER1:R23.1, WAVESHAPER1:WSOUT.P$1
